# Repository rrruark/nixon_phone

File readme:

The project writeup can be found here: http://robruark.com/projects/nixon_phone/nixon_phone.html

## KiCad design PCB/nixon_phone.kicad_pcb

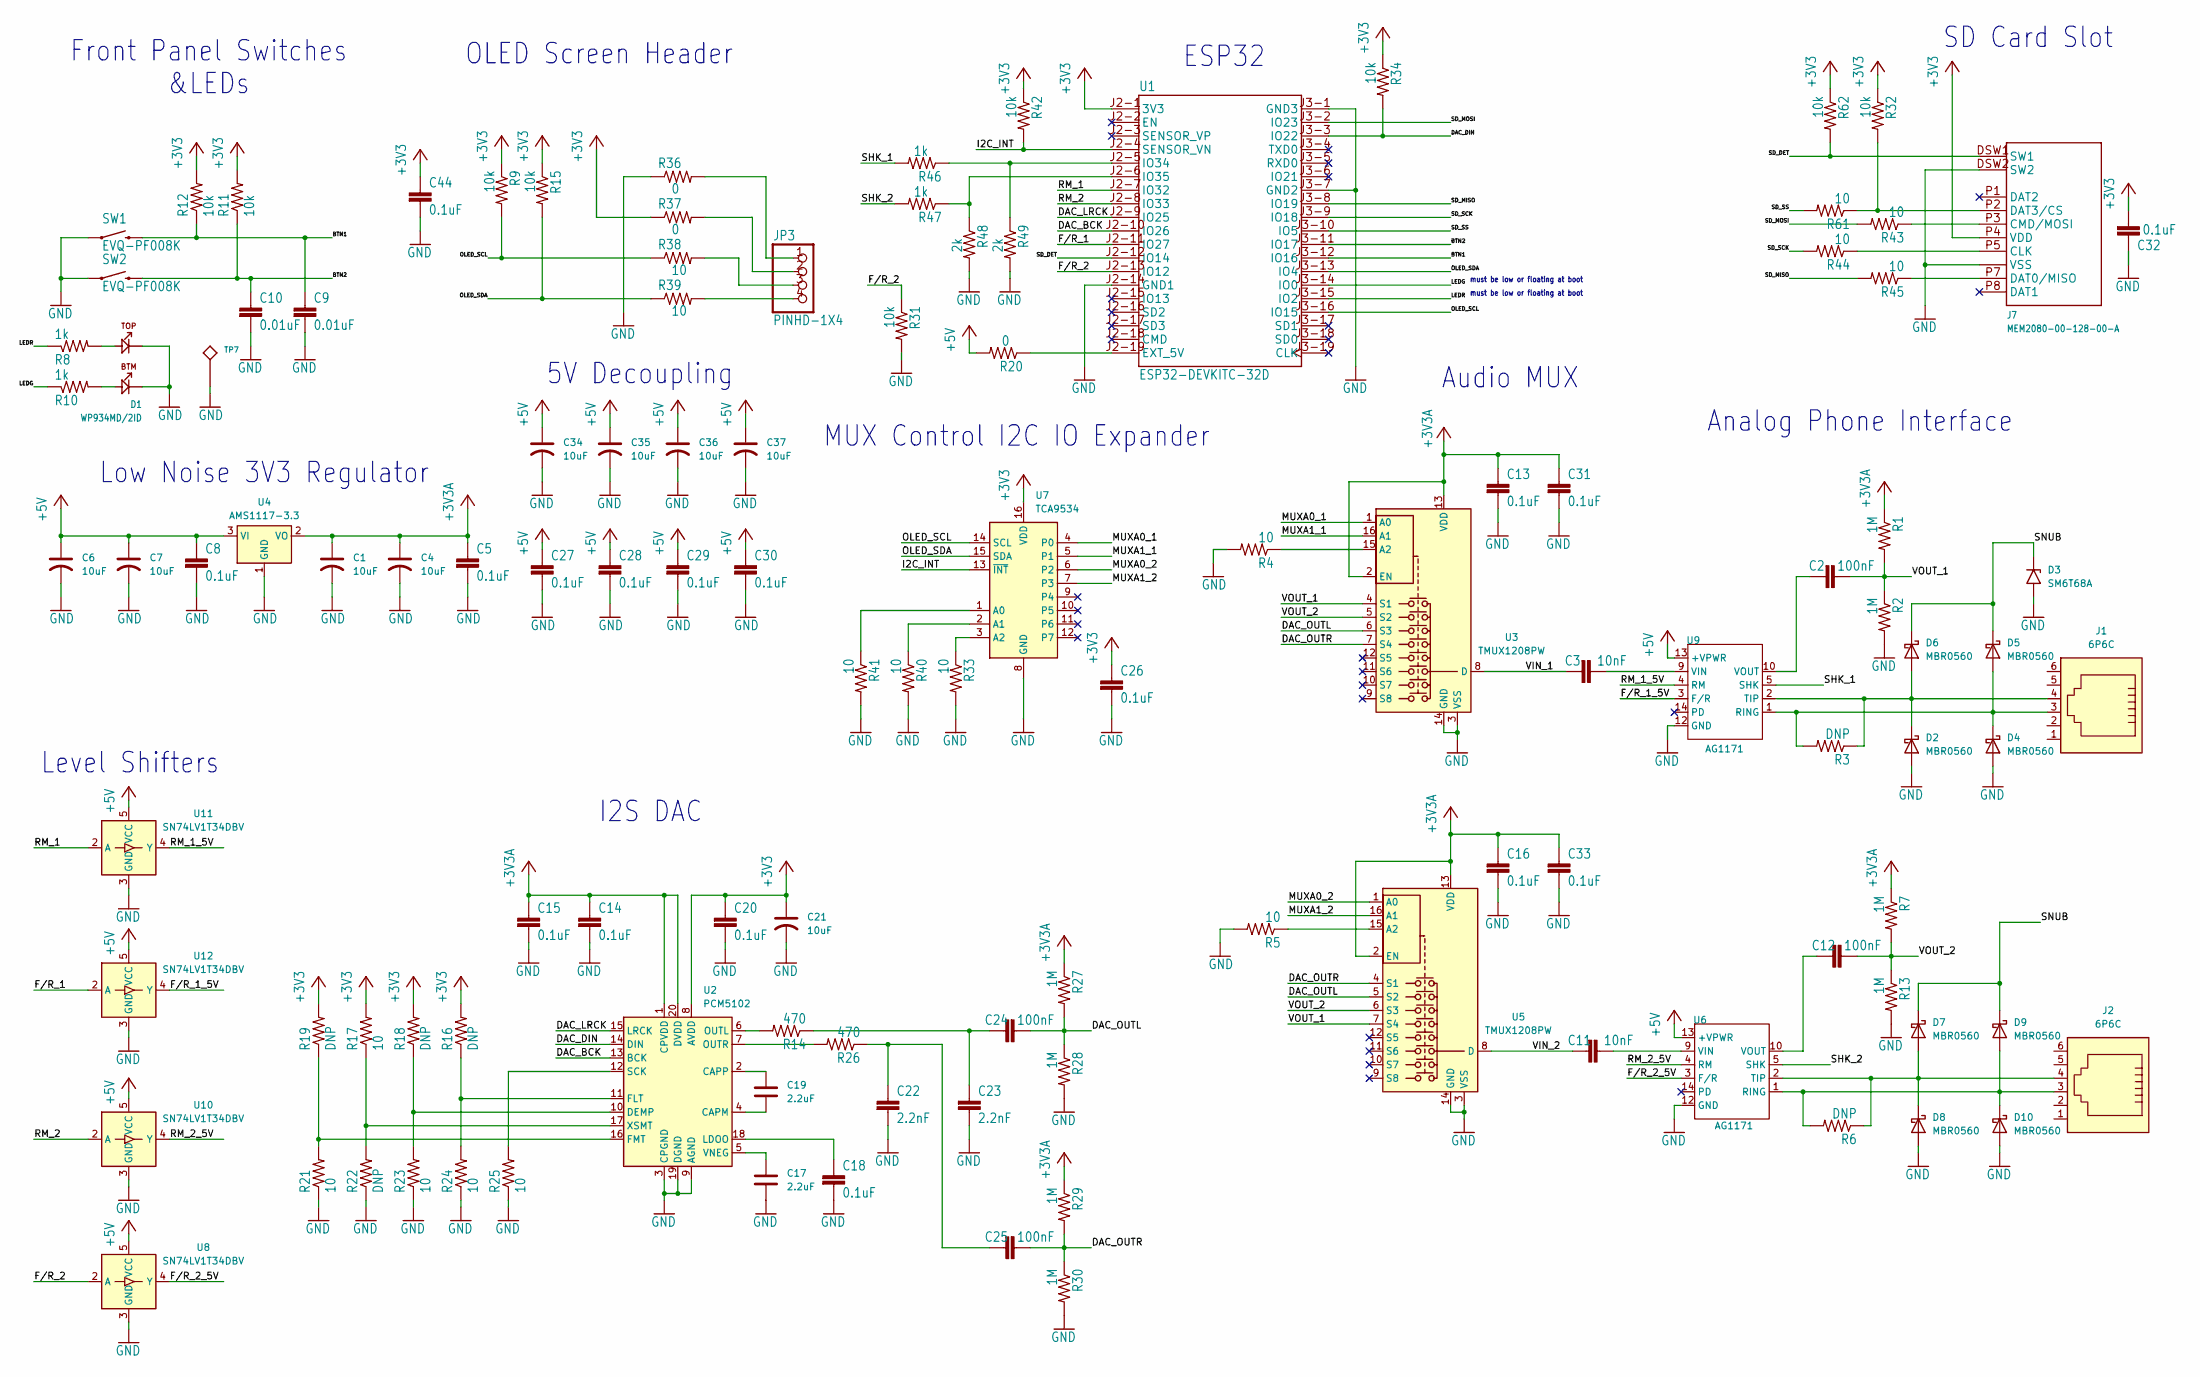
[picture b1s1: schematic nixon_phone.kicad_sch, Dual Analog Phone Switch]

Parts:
C1, C4, C6, C7, C21, C34, C35, C36, C37: 10uF; C_1206_3216Metric_Pad1.33x1.80mm_HandSolder
C2, C12, C24, C25: 100nF; 0603
C3, C11: 10nF; 0603
C5, C8, C13, C14, C15, C16, C18, C20, C26, C27, C28, C29, C30, C31, C32, C33, C44: 0.1uF; 0603
C9, C10: 0.01uF; 0603
C17, C19: 2.2uF; C_0805_2012Metric
C22, C23: 2.2nF; 0603
D1: WP934MD/2ID; WP934MD_2ID
D2, D4, D5, D6, D7, D8, D9, D10: MBR0560; D_SOD-123
D3: SM6T68A; D_SMB
J1, J2: 6P6C; RJ12_Amphenol_54601-x06_Horizontal
J7: MEM2080-00-128-00-A; MEM2080
JP3: PINHD-1X4; 1X04
R1, R2, R7, R13, R27, R28, R29, R30: 1M; 0603
R3, R6, R16, R18, R19, R22: DNP; 0603
R4, R5, R17, R21, R23, R24, R25, R33, R38, R39, R40, R41, R43, R44, R45, R61: 10; 0603
R8, R10, R46, R47: 1k; 0603
R9, R11, R12, R15, R31, R32, R34, R42, R62: 10k; 0603
R14, R26: 470; 0603
R20, R36, R37: 0; 0603
R48, R49: 2k; 0603
SW1, SW2: EVQ-PF008K
TP7: 5011; 5010
U1: ESP32-DEVKITC-32D; MODULE_ESP32-DEVKITC-32D
U2: PCM5102; TSSOP-20_4.4x6.5mm_P0.65mm
U3, U5: TMUX1208PW; TSSOP-16_4.4x5mm_P0.65mm
U4: AMS1117-3.3; SOT-223-3_TabPin2
U6, U9: AG1171; SIP-18
U7: TCA9534; TSSOP-16_4.4x5mm_P0.65mm
U8, U10, U11, U12: SN74LV1T34DBV; SOT-23-5

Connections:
+3V3: C20.1, C21.1, C26.1, C32.2, C44.1, J7.P4 (VDD), R9.1, R11.2, R12.2, R15.1, R16.2, R17.2, R18.2, R19.2, R32.1, R34.1, R37.1, R42.1, R62.1, U1.J2-1 (3V3), U2.8 (AVDD), U7.16 (VDD)
+3V3A: C1.1, C4.1, C5.1, C13.1, C14.1, C15.1, C16.1, C31.1, C33.1, R1.1, R7.1, R27.1, R29.1, U2.1 (CPVDD), U2.20 (DVDD), U3.2 (EN), U3.13 (VDD), U4.2 (VO), U5.2 (EN), U5.13 (VDD)
+5V: C6.1, C7.1, C8.1, C27.1, C28.1, C29.1, C30.1, C34.1, C35.1, C36.1, C37.1, R20.2, U4.3 (VI), U6.13 (+VPWR), U8.5 (VCC), U9.13 (+VPWR), U10.5 (VCC), U11.5 (VCC), U12.5 (VCC)
/BTN1: C9.1, R12.1, SW1.S2 (2), U1.J3-12 (IO16)
/BTN2: C10.1, R11.1, SW2.S2 (2), U1.J3-11 (IO17)
/DAC_BCK: U1.J2-10 (IO26), U2.13 (BCK)
/DAC_DIN: R34.2, U1.J3-3 (IO22), U2.14 (DIN)
/DAC_LRCK: U1.J2-9 (IO25), U2.15 (LRCK)
/DAC_OUTL: C24.1, R27.2, R28.1, U3.6 (S3), U5.5 (S2)
/DAC_OUTR: C25.1, R29.2, R30.1, U3.7 (S4), U5.4 (S1)
/F/R_1: U1.J2-11 (IO27), U12.2 (A)
/F/R_1_5V: U9.3 (F/R), U12.4 (Y)
/F/R_2: R31.1, U1.J2-13 (IO12), U8.2 (A)
/F/R_2_5V: U6.3 (F/R), U8.4 (Y)
/I2C_INT: R42.2, U1.J2-4 (SENSOR_VN), U7.13 (~INT)
/LEDG: R10.1, U1.J3-14 (IO0)
/LEDR: R8.1, U1.J3-15 (IO2)
/MUXA0_1: U3.1 (A0), U7.4 (P0)
/MUXA0_2: U5.1 (A0), U7.6 (P2)
/MUXA1_1: U3.16 (A1), U7.5 (P1)
/MUXA1_2: U5.16 (A1), U7.7 (P3)
/OLED_SCL: R9.2, R38.1, U1.J3-16 (IO15), U7.14 (SCL)
/OLED_SDA: R15.2, R39.1, U1.J3-13 (IO4), U7.15 (SDA)
/RM_1: U1.J2-7 (IO32), U11.2 (A)
/RM_1_5V: U9.4 (RM), U11.4 (Y)
/RM_2: U1.J2-8 (IO33), U10.2 (A)
/RM_2_5V: U6.4 (RM), U10.4 (Y)
/SD_DET: J7.DSW1 (SW1), R62.2, U1.J2-12 (IO14)
/SD_MISO: R45.2, U1.J3-8 (IO19)
/SD_MOSI: R43.2, U1.J3-2 (IO23)
/SD_SCK: R44.2, U1.J3-9 (IO18)
/SD_SS: R61.2, U1.J3-10 (IO5)
/SHK_1: R46.2, U9.5 (SHK)
/SHK_2: R47.2, U6.5 (SHK)
/SNUB: D3.1 (A1), D5.1 (K), D6.1 (K), D7.1 (K), D9.1 (K)
/VIN_1: C3.2, U3.8 (D)
/VIN_2: C11.2, U5.8 (D)
/VOUT_1: C2.1, R1.2, R2.1, U3.4 (S1), U5.7 (S4)
/VOUT_2: C12.1, R7.2, R13.1, U3.5 (S2), U5.6 (S3)
GND: C1.2, C4.2, C5.2, C6.2, C7.2, C8.2, C9.2, C10.2, C13.2, C14.2, C15.2, C16.2, C17.2, C18.2, C20.2, C21.2, C22.2, C23.2, C26.2, C27.2, C28.2, C29.2, C30.2, C31.2, C32.1, C33.2, C34.2, C35.2, C36.2, C37.2, C44.2, D1.K1, D1.K2, D2.2 (A), D3.2 (A2), D4.2 (A), D8.2 (A), D10.2 (A), J7.C1 (VSS), J7.C2 (VSS), J7.C3 (VSS), J7.C4 (VSS), J7.DSW2 (SW2), J7.P6 (VSS), R2.2, R4.2, R5.2, R13.2, R21.1, R22.1, R23.1, R24.1, R25.1, R28.2, R30.2, R31.2, R33.2, R36.1, R40.2, R41.2, R48.2, R49.2, SW1.S1 (1), SW2.S1 (1), TP7.P$1, U1.J2-14 (GND1), U1.J3-1 (GND3), U1.J3-7 (GND2), U2.3 (CPGND), U2.9 (AGND), U2.19 (DGND), U3.3 (VSS), U3.14 (GND), U4.1 (GND), U5.3 (VSS), U5.14 (GND), U6.12 (GND), U7.8 (GND), U8.3 (GND), U9.12 (GND), U10.3 (GND), U11.3 (GND), U12.3 (GND)
unnamed: C22.1, C25.2, R26.1
unnamed: C23.1, C24.2, R14.1
unnamed: D1.A1, R10.2
unnamed: D1.A2, R8.2
unnamed: D2.1 (K), D6.2 (A), J1.4, R3.1, U9.2 (TIP)
unnamed: D4.1 (K), D5.2 (A), J1.3, R3.2, U9.1 (RING)
unnamed: D7.2 (A), D8.1 (K), J2.4, R6.1, U6.2 (TIP)
unnamed: D9.2 (A), D10.1 (K), J2.3, R6.2, U6.1 (RING)
unnamed: J7.P5 (CLK), R44.1
unnamed: J7.P3 (CMD/MOSI), R43.1
unnamed: J7.P7 (DAT0/MISO), R45.1
unnamed: J7.P2 (DAT3/CS), R32.2, R61.1
unnamed: JP3.1, R36.2
unnamed: JP3.2, R37.2
unnamed: JP3.3, R38.2
unnamed: JP3.4, R39.2
unnamed: R20.1, U1.J2-19 (EXT_5V)
unnamed: R46.1, R49.1, U1.J2-5 (IO34)
unnamed: R47.1, R48.1, U1.J2-6 (IO35)
unnamed: C19.2, U2.4 (CAPM)
unnamed: C19.1, U2.2 (CAPP)
unnamed: R18.1, R23.2, U2.10 (DEMP)
unnamed: R16.1, R24.2, U2.11 (FLT)
unnamed: R19.1, R21.2, U2.16 (FMT)
unnamed: C18.1, U2.18 (LDOO)
unnamed: R14.2, U2.6 (OUTL)
unnamed: R26.2, U2.7 (OUTR)
unnamed: R25.2, U2.12 (SCK)
unnamed: C17.1, U2.5 (VNEG)
unnamed: R17.1, R22.2, U2.17 (XSMT)
unnamed: R4.1, U3.15 (A2)
unnamed: R5.1, U5.15 (A2)
unnamed: C11.1, U6.9 (VIN)
unnamed: C12.2, U6.10 (VOUT)
unnamed: R41.1, U7.1 (A0)
unnamed: R40.1, U7.2 (A1)
unnamed: R33.1, U7.3 (A2)
unnamed: C3.1, U9.9 (VIN)
unnamed: C2.2, U9.10 (VOUT)

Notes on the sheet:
SD Card Slot
Front Panel Switches &LEDs
must be low or floating at boot
Low Noise 3V3 Regulator
Audio MUX
I2S DAC
5V Decoupling
OLED Screen Header
MUX Control I2C IO Expander
Level Shifters
ESP32
Analog Phone Interface

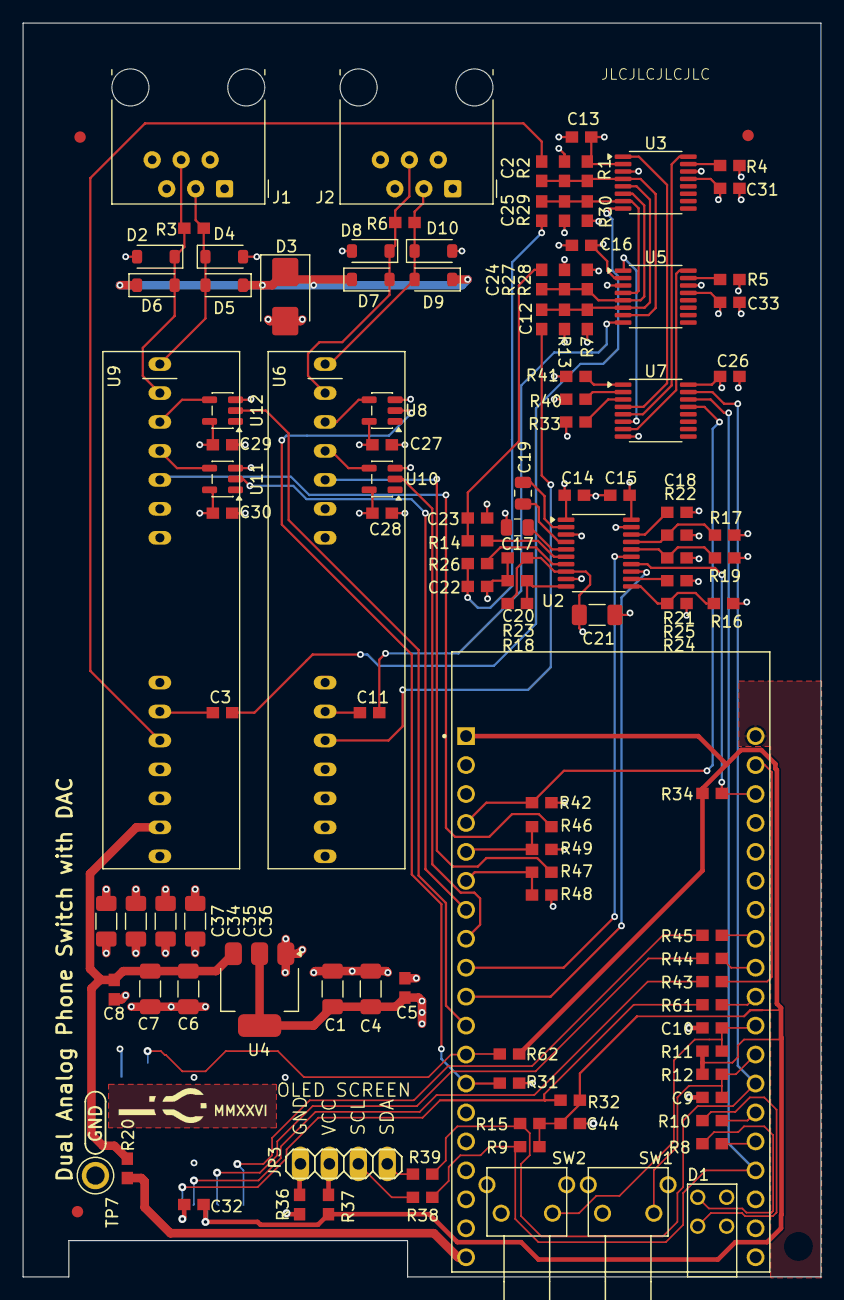
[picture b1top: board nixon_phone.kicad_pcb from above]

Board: 4 copper layers, 70.0 x 110.0 mm, 117 parts (1 on the bottom side), 79 nets.

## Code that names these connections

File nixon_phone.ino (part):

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#include <math.h>

// PCM5102 DAC Pin Definitions
#define I2S_BCK_PIN    26  // IO26: DAC_BCK (Bit Clock)
#define I2S_LRCLK_PIN  25  // IO25: DAC_LRCLK (Left/Right Clock)
#define I2S_DIN_PIN    22  // IO22: DAC_DIN (Data Input)

// SLIC Control Pins
#define SHK_1_PIN      34  // IO34: SHK_1
#define SHK_2_PIN      35  // IO35: SHK_2
#define RM_1_PIN       32  // IO32: RM_1
#define RM_2_PIN       33  // IO33: RM_2
#define FR_1_PIN       27  // IO27: F/R_1
#define FR_2_PIN       12  // IO12: F/R_2

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#define BUTTON_2_PIN   17  // IO17: BUTTON_2

// SD Card Pins (SPI)
#define SD_SS_PIN      5   // IO5: SD_SS
#define SD_SCK_PIN     18  // IO18: SD_SCK
#define SD_MISO_PIN    19  // IO19: SD_MISO
#define SD_MOSI_PIN    23  // IO23: SD_MOSI

// I2C Pins
#define I2C_SDA_PIN    4   // IO4: OLED_SDA (shared with TCA9534)
#define I2C_SCL_PIN    15  // IO15: OLED_SCK (shared with TCA9534)

// TCA9534 GPIO Expander
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#define TCA9534_REG_CONFIG         0x03  // Configuration register (0=output, 1=input)

// TCA9534 Pin definitions
#define TCA9534_MUXA0_1    0  // P0: MUXA0_1
#define TCA9534_MUXA1_1    1  // P1: MUXA1_1
#define TCA9534_MUXA0_2    2  // P2: MUXA0_2
#define TCA9534_MUXA1_2    3  // P3: MUXA1_2

// I2S Configuration
#define SAMPLE_RATE    44100
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  uint8_t shk_pin;  // SHK pin for the phone being rung (off-hook = stop ringing)
  
  if (phoneNum == 1) {
    rm_pin = RM_1_PIN;
    fr_pin = FR_1_PIN;
    shk_pin = SHK_1_PIN;
    Serial.println("Ringing phone 1...");
  } else if (phoneNum == 2) {
    rm_pin = RM_2_PIN;
    fr_pin = FR_2_PIN;
    shk_pin = SHK_2_PIN;
    Serial.println("Ringing phone 2...");
  } else {
    Serial.println("Invalid phone number");
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  initDialToneTable();
  
  // Configure SHK pins as inputs with pull-up resistors
  pinMode(SHK_1_PIN, INPUT_PULLUP);
  pinMode(SHK_2_PIN, INPUT_PULLUP);
  
  // Initialize previous state of SHK pins
  prev_shk_1_state = digitalRead(SHK_1_PIN);
  prev_shk_2_state = digitalRead(SHK_2_PIN);
  
  // Configure LED pins as outputs
  pinMode(LED_RED_PIN, OUTPUT);
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  digitalWrite(LED_GREEN_PIN, HIGH);  // Green LED on by default
  
  // Configure RM pins as outputs and set them low
  pinMode(RM_1_PIN, OUTPUT);
  pinMode(RM_2_PIN, OUTPUT);
  digitalWrite(RM_1_PIN, LOW);
  digitalWrite(RM_2_PIN, LOW);
  
  // Configure F/R pins as outputs and set them low
  pinMode(FR_1_PIN, OUTPUT);
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  
  // Initialize SD card
  Serial.println("Initializing SD card...");
  SPI.begin(SD_SCK_PIN, SD_MISO_PIN, SD_MOSI_PIN, SD_SS_PIN);
  
  // Set SPI clock to 4 MHz for stable SD card operation
  if (!SD.begin(SD_SS_PIN, SPI, 4000000)) {
    Serial.println("SD card initialization failed!");
    Serial.println("Please check:");
    Serial.println("1. Is the SD card inserted?");
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  
  // Monitor SHK pins and control LED_GREEN and playback
  // If SHK_1 OR SHK_2 is high, set LED_GREEN high; if both are low, set it low
  bool shk_1_state = digitalRead(SHK_1_PIN);
  bool shk_2_state = digitalRead(SHK_2_PIN);
  bool shk_any_high = shk_1_state || shk_2_state;
  
  // Detect rotary dial pulses (must be called before updating prev_shk states)
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
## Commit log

2026-02-01 Adding example audio files
2026-02-01 add feature to cease ringing when called party goes off hook.
2026-05-17 Adding plates
2026-05-17 adding readme
2026-05-17 fixing readme
